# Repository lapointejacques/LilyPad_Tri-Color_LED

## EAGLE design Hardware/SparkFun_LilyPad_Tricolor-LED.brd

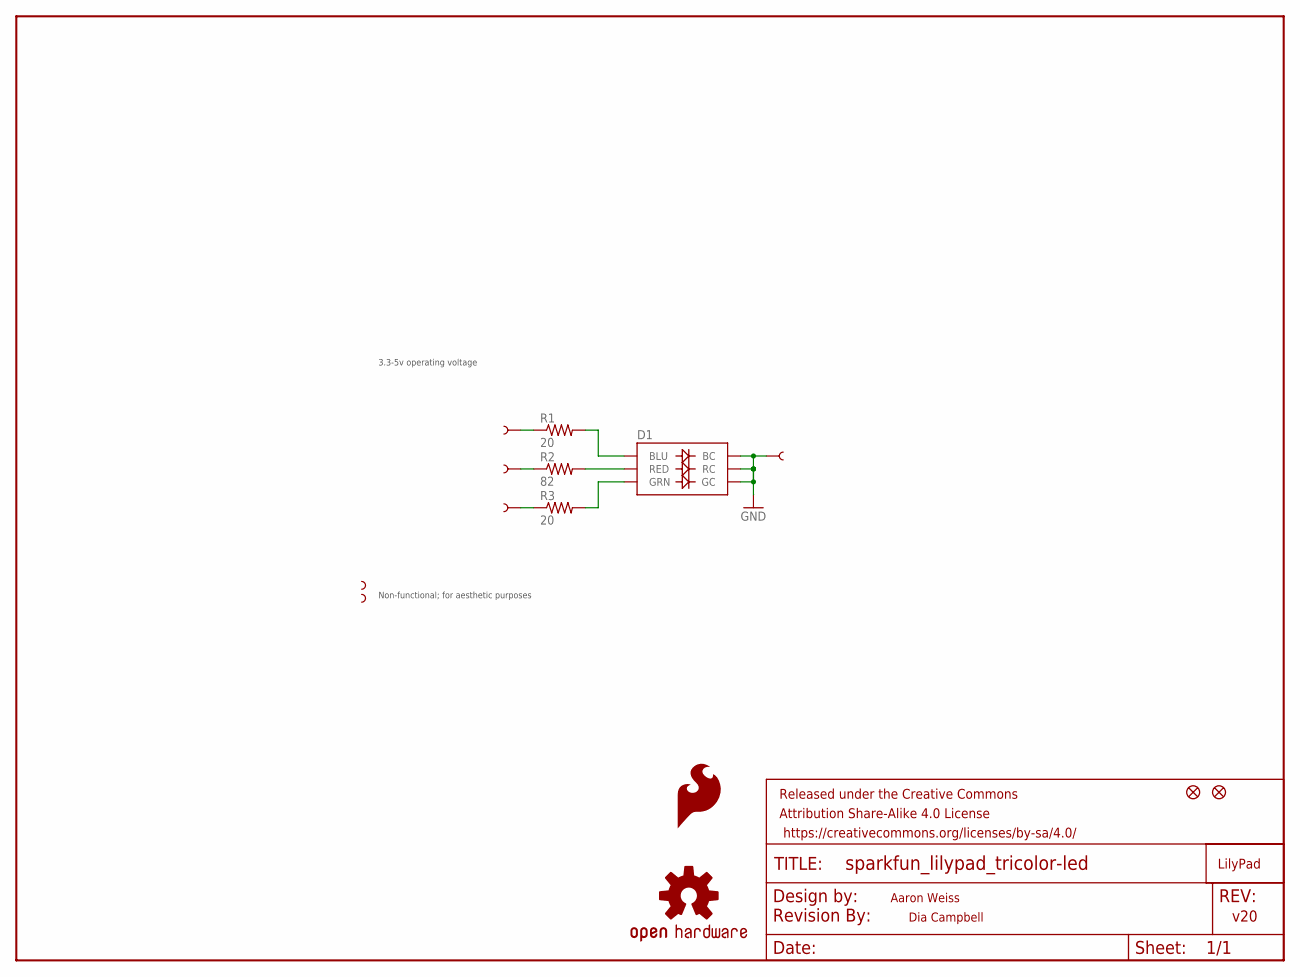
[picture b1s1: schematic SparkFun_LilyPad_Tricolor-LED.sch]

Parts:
BLU: SEWTAP6; PETAL-SMALL-2SIDE
D1: LED-TRICOLOR-NO-COMPLCC-6-SMD; PLCC-6-LED
FID1, FID2: FIDUCIAL1X2; FIDUCIAL-1X2
FRAME1: FRAME-LETTER; CREATIVE_COMMONS
GND: SEWTAP6; PETAL-SMALL-2SIDE
GRN: SEWTAP6; PETAL-SMALL-2SIDE
LOGO1: OSHW-LOGOS; OSHW-LOGO-S
LOGO2: SFE_LOGO_FLAME.1_INCH; SFE_LOGO_FLAME_.1
R1, R3: 20; 0603-RES
R2: 82; 0603-RES
RED: SEWTAP6; PETAL-SMALL-2SIDE
U$1: LOGO-LPLP; LOGO-LILYPAD
U$2, U$3: SEWTAP-NOHOLE2; PETAL-NOHOLE-2SIDE
U$4: REVISION

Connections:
BLU: D1.AB (BLU), R1.2
GND: D1.CB (BC), D1.CG (GC), D1.CR (RC), GND.1
GRN: D1.AG (GRN), R3.2
unnamed: BLU.1, R1.1
unnamed: R2.1, RED.1
unnamed: GRN.1, R3.1
RED: D1.AR (RED), R2.2

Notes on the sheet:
v20
Aaron Weiss
Non-functional; for aesthetic purposes
3.3-5v operating voltage
Dia Campbell

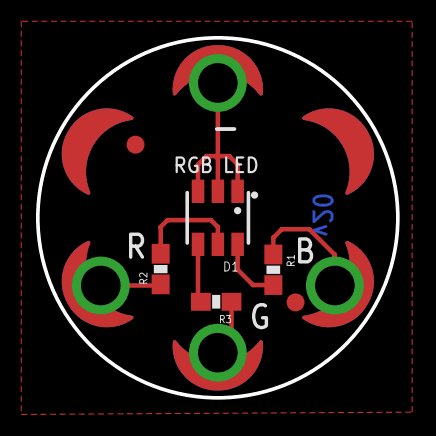
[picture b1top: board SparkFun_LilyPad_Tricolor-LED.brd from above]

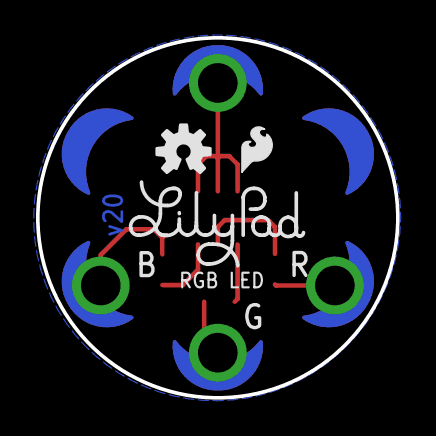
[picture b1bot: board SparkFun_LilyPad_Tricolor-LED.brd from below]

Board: 2 copper layers, 20.0 x 20.0 mm, 17 parts (3 on the bottom side), 7 nets.

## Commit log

2015-06-04 Changed to common cathode LED, changed resistors
2015-06-04 Small schematic correction, fixed version number
2015-08-13 Small logo movement, couple of checklist changes
2015-08-20 Checklist tweaks to the schematic
2015-10-14 Added ground pours to conform to new aesthetic standard
2015-12-02 Changes to meet new design standards
2015-12-07 Adding na,e
2015-12-07 Fiducial adjustment
2015-12-10 Added extra silk *only for protos*
2015-12-22 moved ground pour, added silk for review
2016-02-05 Re-ordered pins, added silk

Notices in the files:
parts and their libraries:
SparkFun-Aesthetics: Licensing: Creative Commons ShareAlike 4.0 International - https://creativecommons.org/licenses/by-sa/4.0
SparkFun-Aesthetics: Released under the Creative Commons Attribution Share-Alike 4.0 License
SparkFun-Aesthetics: https://creativecommons.org/licenses/by-sa/4.0
